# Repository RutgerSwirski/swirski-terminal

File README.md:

# Swirski Terminal

Swirski Terminal is a small wearable terminal built around an ESP32-S3,
an ILI9341 display, LVGL, and a rotary encoder. An Android companion app sends
notifications, media state, time, and Wi-Fi configuration over an encrypted
BLE connection.

The shared C++ application can also run as an SDL desktop build for faster UI
development and protocol testing.

## Current Features

- Notification snapshots, live notifications, detail views, and toasts
- Music state, progress, play/pause, previous, and next controls
- BLE pairing, bonding, chunked messages, and automatic reconnection
- Wi-Fi scanning, connection management, signal status, and internet testing
- Phone-synchronized date and time with persistent fallback
- Rotary encoder navigation, virtual keyboard, settings, and optional screen timeout
- Automatic Wi-Fi and BLE reconnection after transient disconnects
- Pong and Blackjack
- Shared LVGL screens and services across ESP32 and desktop targets

## Repository Layout

```text
app/      Shared C++ application, screens, services, protocol, and UI
desktop/  SDL/LVGL desktop simulator and C++ tests
esp32/    ESP-IDF firmware, hardware input, display, Wi-Fi, and BLE transport
mobile/   React Native Android companion app
docs/     Protocol documentation
```

## Desktop Build

Requirements:

- CMake 3.22 or newer
- Ninja
- A C++20 compiler
- SDL2 development files

Build and launch the simulator from the repository root:

```bash
./buildDesktop.sh
```

Run the C++ tests after building:

```bash
ctest --test-dir desktop/build --output-on-failure
```

## ESP32 Build

The firmware currently targets an ESP32-S3 with 4 MB flash, an ILI9341
320x240 SPI display, a rotary encoder, and a back button. Hardware pins are
defined near the top of `esp32/main/main.cpp` and in `esp32/main/inputs/`.
The display backlight uses an inverted BC327 PWM stage on GPIO 12. Brightness
can be adjusted from 10–100% in 10% steps in Settings, is retained across
restarts, and the backlight switches off with the display timeout.
The 30-second screen sleep can also be disabled in Settings to keep the display
on, and that choice is retained across restarts.
Settings also provides confirmed reboot and power-off actions. Power-off uses
ESP32 deep sleep because the current hardware has no software-controlled load
switch; press either the rotary knob or back button to start it again.

The MAX17048 fuel gauge is read at I2C address `0x36` every five seconds.
For the current direct-GPIO prototype, connect it as follows:

- MAX17048 SDA to ESP32-S3 GPIO 1
- MAX17048 SCL to ESP32-S3 GPIO 2
- MAX17048 VIN to 3.3 V and GND to GND

The two JST-PH battery sockets on the breakout are a pass-through pair: connect
the single-cell LiPo to either socket and the terminal's power/charging path to
the other. Battery voltage is retained in system state as millivolts, charge
percentage is shown in the status bar, and both readings are logged at debug
level. The PCB-v1 schematic instead reserves GPIO 8/9 for its shared I2C bus;
those pins must not be selected in this prototype firmware while the back and
encoder switches still use direct GPIO.

Install ESP-IDF, then build from the `esp32` directory:

```bash
source "$HOME/.espressif/v6.0.2/esp-idf/export.sh"
idf.py build
```

Flash and monitor a connected device:

```bash
idf.py -p /dev/ttyACM0 -b 115200 flash monitor
```

Change the serial port when your device appears under a different path.

Pushes to `main` that change `app/` or `esp32/` automatically build the
firmware and update the `firmware-latest` GitHub Release. The release asset is
published as `swirski_os_esp32.bin` for the terminal's OTA updater. The same
workflow can also be started manually from the GitHub Actions page.

## Android Companion

Requirements:

- Node.js 22.11 or newer
- Android Studio and the Android SDK
- A physical Android device with Bluetooth Low Energy

Install dependencies and start Metro:

```bash
cd mobile
npm install
npm start
```

In another terminal, install the debug app:

```bash
cd mobile
npm run android
```

Android notification-listener access is required for notification sync and
media discovery. The app prompts for the relevant Bluetooth and notification
permissions when needed.

Pushes to `main` that change `mobile/` automatically build the Android app and
replace the rolling `mobile-latest` GitHub Release. The app checks that
release's small manifest when it opens and shows **Mobile update available**
when its installed build number is older. The download opens in Android's
normal APK installation flow.

The rolling workflow requires the same permanent signing key for every build so
Android can install each APK over the previous one. Reuse and securely back up
the key that signed any APK already installed on your phone. Only generate a
new key if there is no existing release key:

```bash
keytool -genkeypair -v \
  -keystore swirski-upload.jks \
  -alias swirski-upload \
  -keyalg RSA \
  -keysize 2048 \
  -validity 10000
```

Configure these repository secrets before running the workflow, replacing the
example path with the existing key when applicable:

```bash
base64 -w 0 path/to/swirski-upload.jks | gh secret set SWIRSKI_UPLOAD_KEYSTORE_BASE64
gh secret set SWIRSKI_UPLOAD_STORE_PASSWORD
gh secret set SWIRSKI_UPLOAD_KEY_ALIAS
gh secret set SWIRSKI_UPLOAD_KEY_PASSWORD
```

Use the alias entered above (`swirski-upload` in the example). The last three
commands prompt for their values. Never commit the key or passwords. Losing
the key means future APKs cannot update existing installations.

Local standalone builds made by `mobile/deploy.sh` use Android's development
key unless the same `SWIRSKI_UPLOAD_*` environment variables are supplied. If
the app currently installed on a phone uses that development key, uninstall it
once before installing the first `mobile-latest` APK, then re-enable Android's
notification-listener access. Subsequent rolling releases install as updates.

## Protocol

Messages use a versioned JSON envelope. Larger BLE messages are divided into
frames and reassembled by the receiver. See
[`docs/ble-framing.md`](docs/ble-framing.md) for the framing format.

## License

This project is available under the [MIT License](LICENSE).

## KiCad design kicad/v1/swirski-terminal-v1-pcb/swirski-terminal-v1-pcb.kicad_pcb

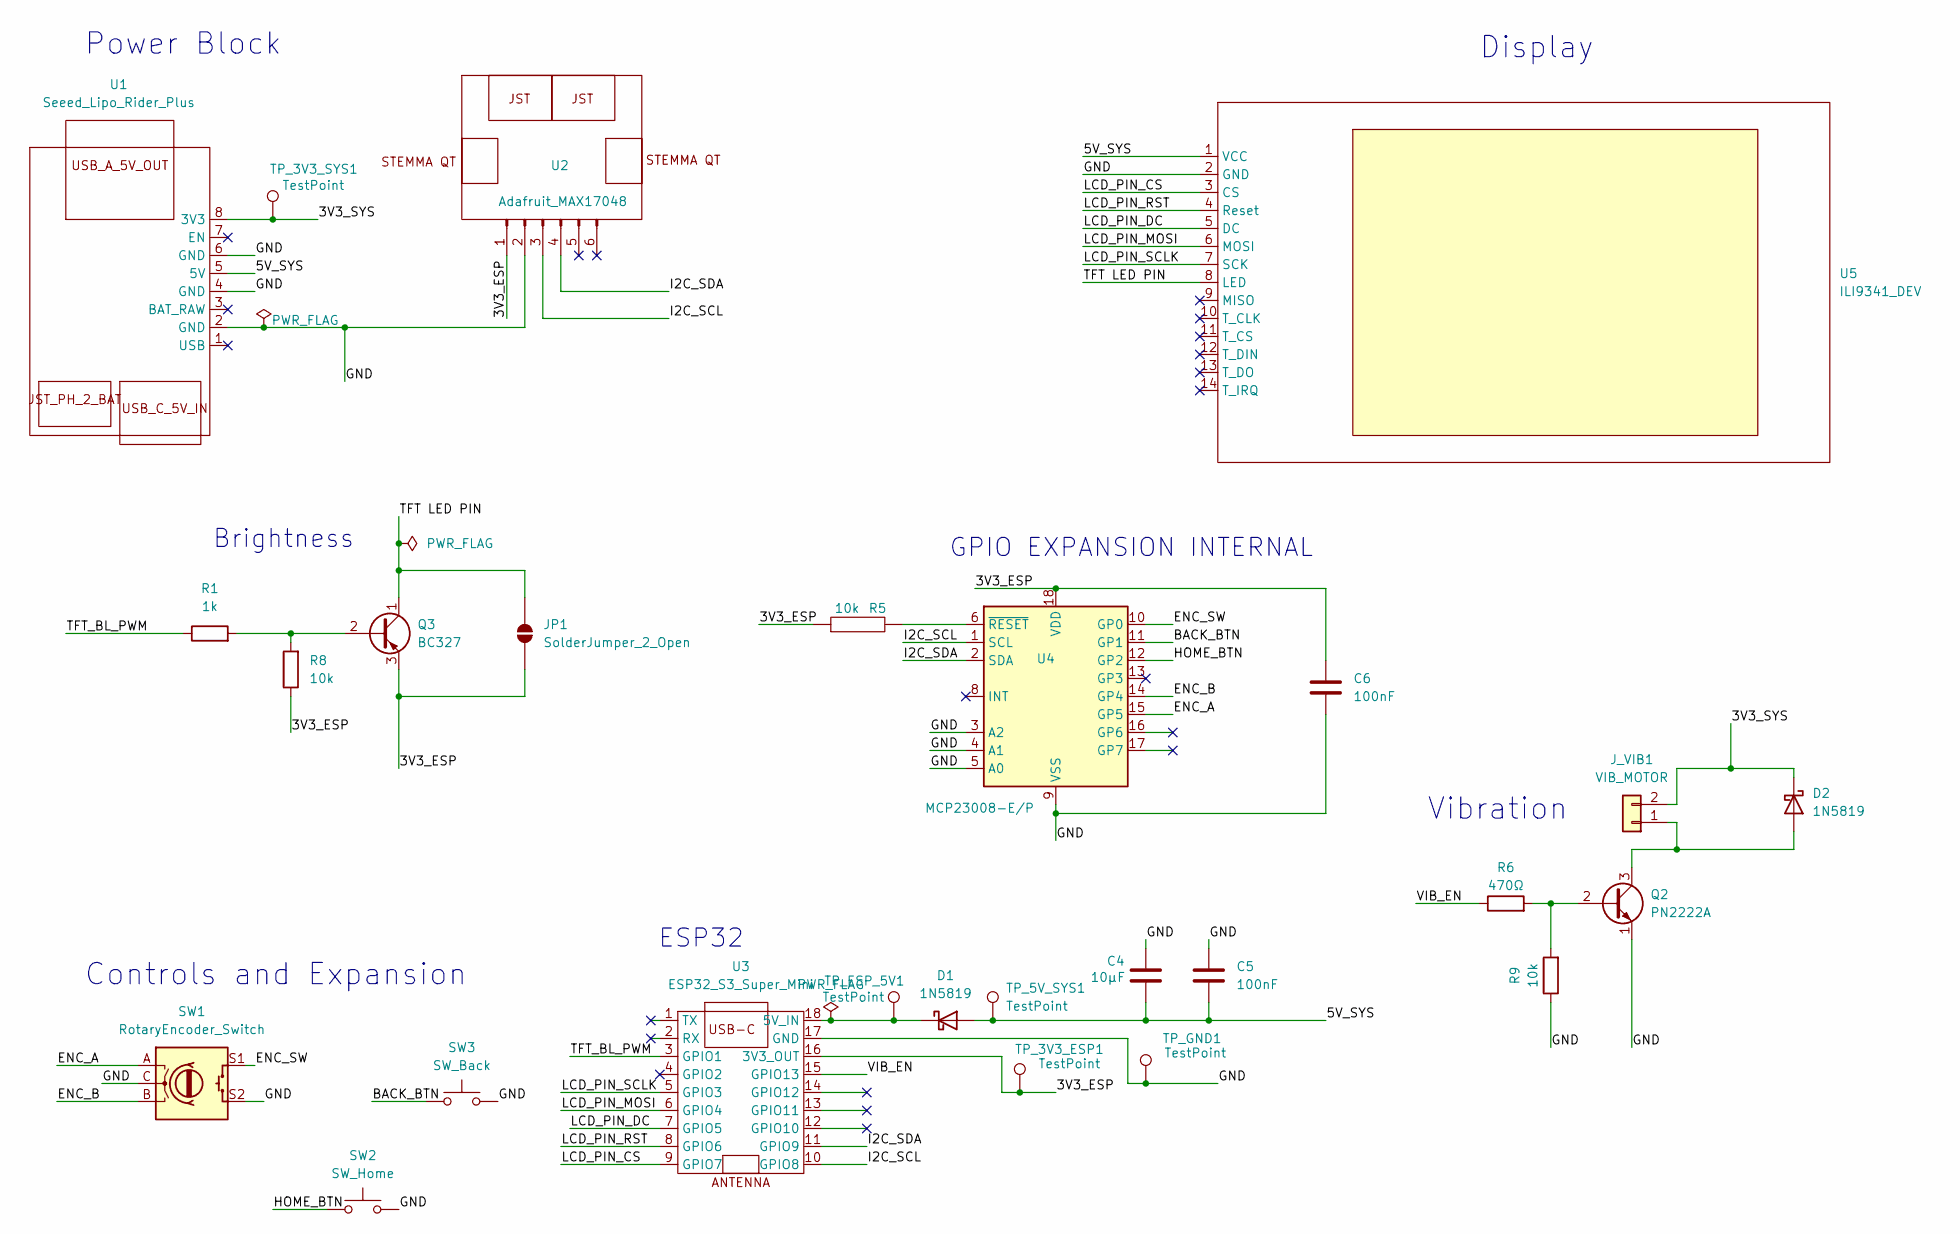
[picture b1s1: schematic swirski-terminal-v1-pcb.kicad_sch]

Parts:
C4: 10µF; CP_Radial_D5.0mm_P2.00mm
C5, C6: 100nF; C_Disc_D5.0mm_W2.5mm_P5.00mm
D1, D2: 1N5819; D_DO-41_SOD81_P10.16mm_Horizontal
JP1: SolderJumper_2_Open; PinHeader_1x02_P2.54mm_Vertical
J_VIB1: VIB_MOTOR; PinHeader_1x02_P2.54mm_Vertical
Q2: PN2222A; TO-92_Inline
Q3: BC327; TO-92_Inline
R1: 1k; R_Axial_DIN0207_L6.3mm_D2.5mm_P10.16mm_Horizontal
R5, R8, R9: 10k; R_Axial_DIN0207_L6.3mm_D2.5mm_P10.16mm_Horizontal
R6: 470Ω; R_Axial_DIN0207_L6.3mm_D2.5mm_P10.16mm_Horizontal
SW1: RotaryEncoder_Switch; RotaryEncoder_Alps_EC11E-Switch_Vertical_H20mm
SW2: SW_Home; SW_PUSH_6mm
SW3: SW_Back; SW_PUSH_6mm
TP_3V3_ESP1, TP_3V3_SYS1, TP_5V_SYS1: TestPoint; TestPoint_Loop_D2.50mm_Drill1.0mm
TP_ESP_5V1: TestPoint; TestPoint_Loop_D2.50mm_Drill1.0mm
TP_GND1: TestPoint; TestPoint_Loop_D2.50mm_Drill1.0mm
U1: Seeed_Lipo_Rider_Plus; Seeed_LiPo_Rider_Plus
U2: Adafruit_MAX17048; Adafruit_MAX17048_Breakout
U3: ESP32_S3_Super_Mini; ESP32_S3_SUPER_MINI_2x09Pins
U4: MCP23008-E/P; DIP-18_W7.62mm
U5: ILI9341_DEV; ILI9341_DEV_14Pin

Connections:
/3V3_ESP: C6.1, JP1.1 (A), Q3.3 (E), R5.1, R8.1, TP_3V3_ESP1.1 (1_1), U2.1 (VIN), U3.16 (3V3_OUT), U4.18 (VDD)
/3V3_SYS: D2.1 (K), J_VIB1.2, TP_3V3_SYS1.1 (1_1), U1.8 (3V3)
/5V_SYS: C4.2, C5.2, D1.2 (A), TP_5V_SYS1.1 (1_1), U1.5 (5V), U5.1 (VCC)
/BACK_BTN: SW3.1, U4.11 (GP1)
/ENC_A: SW1.A, U4.15 (GP5)
/ENC_B: SW1.B, U4.14 (GP4)
/ENC_SW: SW1.S1, U4.10 (GP0)
/EXTRA_GPIO_1: U4.13 (GP3)
/GND: C4.1, C5.1, C6.2, Q2.1 (E), R9.1, SW1.C, SW1.S2, SW2.2, SW3.2, TP_GND1.1 (1_1), U1.2 (GND), U1.4 (GND), U1.6 (GND), U2.2 (GND), U3.17 (GND), U4.3 (A2), U4.4 (A1), U4.5 (A0), U4.9 (VSS), U5.2 (GND)
/HOME_BTN: SW2.1, U4.12 (GP2)
/I2C_SCL: U2.3 (SCL), U3.10 (GPIO8), U4.1 (SCL)
/I2C_SDA: U2.4 (SDA), U3.11 (GPIO9), U4.2 (SDA)
/LCD_PIN_CS: U3.9 (GPIO7), U5.3 (CS)
/LCD_PIN_DC: U3.7 (GPIO5), U5.5 (DC)
/LCD_PIN_MOSI: U3.6 (GPIO4), U5.6 (MOSI)
/LCD_PIN_RST: U3.8 (GPIO6), U5.4 (Reset)
/LCD_PIN_SCLK: U3.5 (GPIO3), U5.7 (SCK)
/TFT LED PIN: JP1.2 (B), Q3.1 (C), U3.4 (GPIO2), U5.8 (LED)
/TFT_BL_PWM: R1.1, U3.3 (GPIO1)
/VIB_EN: R6.1, U3.15 (GPIO13)
unnamed: D1.1 (K), TP_ESP_5V1.1 (1_1), U3.18 (5V_IN)
unnamed: D2.2 (A), J_VIB1.1, Q2.3 (C)
unnamed: Q2.2 (B), R6.2, R9.2
unnamed: Q3.2 (B), R1.2, R8.2
unnamed: R5.2, U4.6 (~RESET)

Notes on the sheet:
Power Block
Controls and Expansion
Vibration
Display
ESP32
GPIO EXPANSION INTERNAL
Brightness

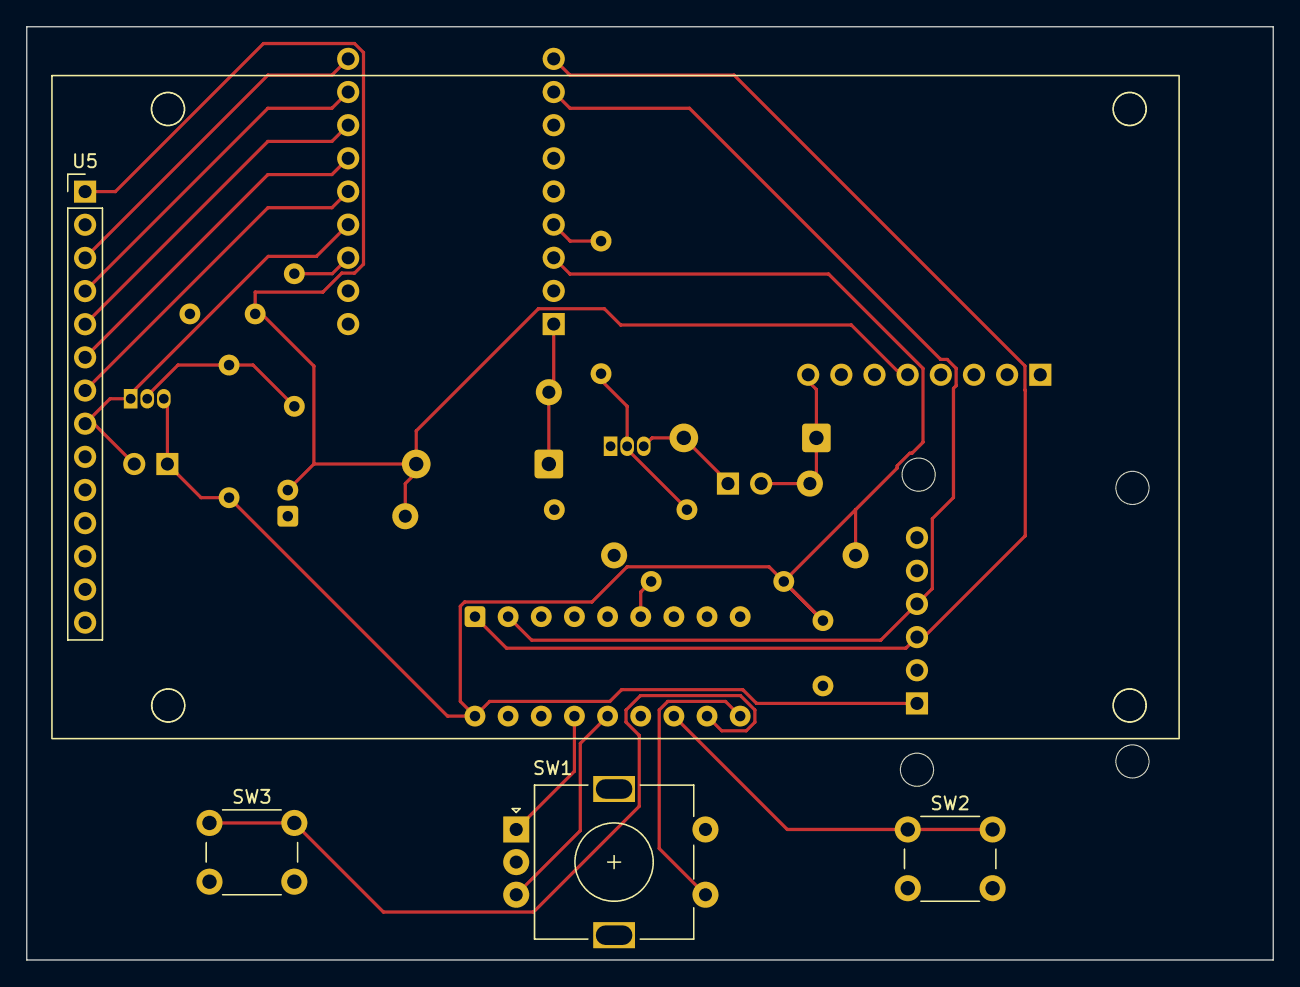
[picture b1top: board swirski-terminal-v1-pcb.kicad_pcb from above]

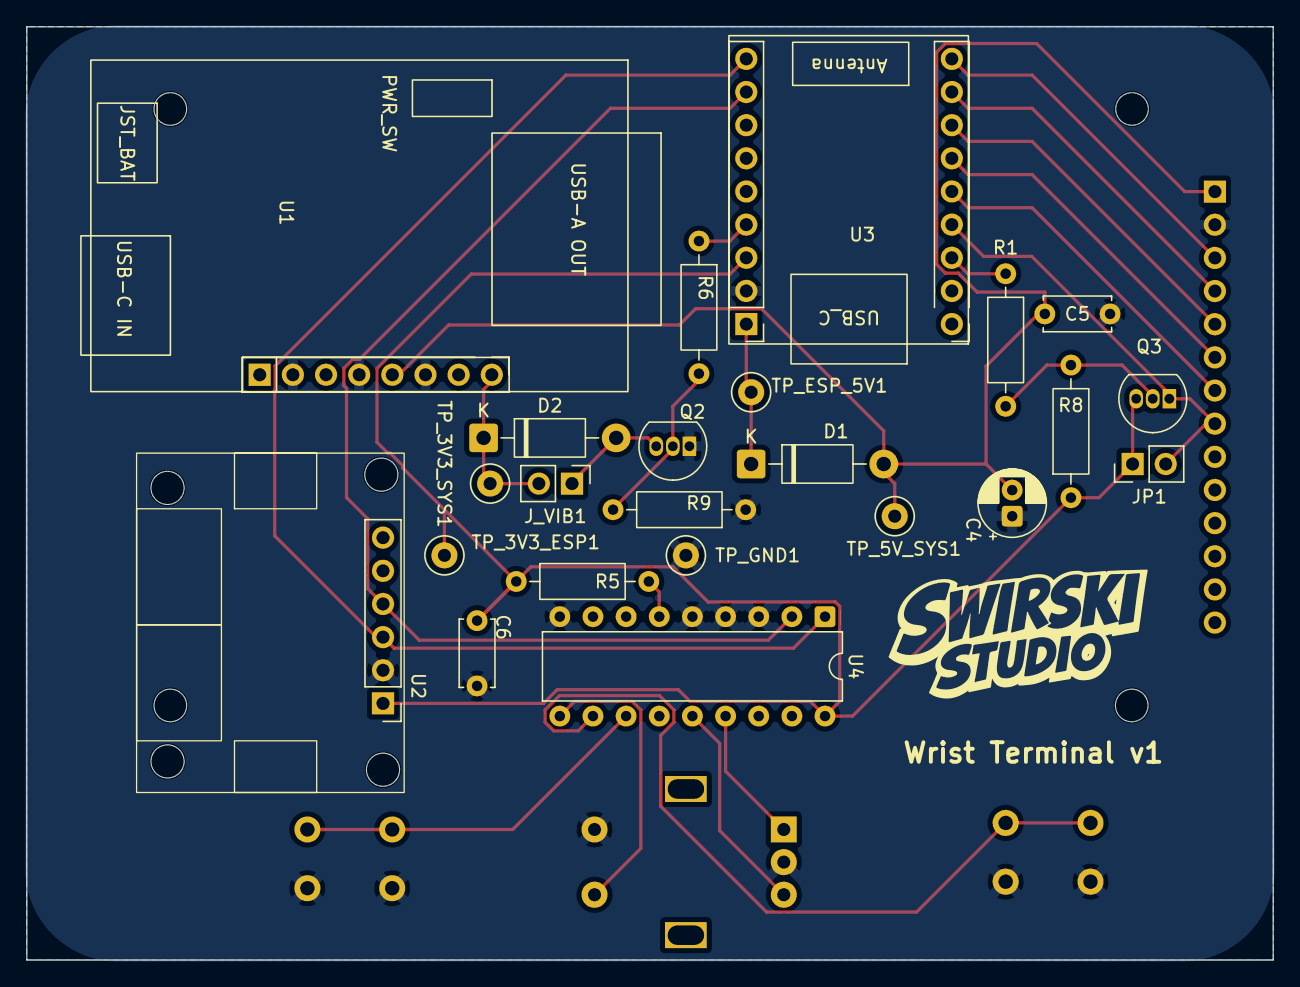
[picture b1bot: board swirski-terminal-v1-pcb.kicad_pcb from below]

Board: 2 copper layers, 95.5 x 71.5 mm, 27 parts (23 on the bottom side), 24 nets.

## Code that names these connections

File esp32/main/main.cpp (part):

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
    constexpr spi_host_device_t LCD_HOST = SPI2_HOST;

    constexpr gpio_num_t LCD_PIN_MOSI = GPIO_NUM_6;
    constexpr gpio_num_t LCD_PIN_SCLK = GPIO_NUM_7;
    constexpr gpio_num_t LCD_PIN_CS = GPIO_NUM_5;
    constexpr gpio_num_t LCD_PIN_DC = GPIO_NUM_4;
    constexpr gpio_num_t LCD_PIN_RST = GPIO_NUM_3;
    constexpr gpio_num_t BACK_BUTTON_PIN = GPIO_NUM_8;
    constexpr gpio_num_t ROTARY_BUTTON_PIN = GPIO_NUM_9;

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
    spi_bus_config_t busConfig{};

    busConfig.sclk_io_num = LCD_PIN_SCLK;
    busConfig.mosi_io_num = LCD_PIN_MOSI;
    busConfig.miso_io_num = -1;
    busConfig.quadwp_io_num = -1;
    busConfig.quadhd_io_num = -1;
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
    esp_lcd_panel_io_spi_config_t ioConfig{};

    ioConfig.cs_gpio_num = LCD_PIN_CS;
    ioConfig.dc_gpio_num = LCD_PIN_DC;
    ioConfig.spi_mode = 0;
    ioConfig.pclk_hz = 40 * 1000 * 1000;
    ioConfig.trans_queue_depth = 10;
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
    esp_lcd_panel_dev_config_t panelConfig{};

    panelConfig.reset_gpio_num = LCD_PIN_RST;
    panelConfig.rgb_ele_order = LCD_RGB_ELEMENT_ORDER_BGR;
    panelConfig.bits_per_pixel = 16;

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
